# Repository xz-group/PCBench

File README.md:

# PCBench

PCBench is a free open-source benckmark for board-level hardware attacks and Trojans.

## What's News

Version 1.0

This is the initial release of the benchmars for board-level hardware security.

## Motivation
Most modern electronic systems are hosted by printed circuit boards(PCBs), making them a ubiquitous system component that can take many different shapes and forms. In order to achieve a high level of economy of scale, the global supply chain of electronic systems has evolved into disparate segments for the design, fabrication, assembly, and testing of PCB boards and their various associated components. <br />
As a consequence, the modern PCB supply chain exposes many vulnerabilities along its different stages, allowing adversaries to introduce malicious alterations to facilitate board-level attacks. As an emerging hardware threat, the attack and defense techniques at the board level have not yet been systemically explored and thus require a thorough and comprehensive investigation. <br />
In the absence of a standard board-level attack benchmark, current re-search on perspective countermeasures is likely to be evaluated on proprietary variants of ad-hoc attacks, preventing credible and verifiable comparison among different techniques. Upon this request, we have created the PCBench, which is a set of board-level attack benchmarks for open-source release.

## Benchmarking Methodology

We generated the benchmarks based on the methodology proposed in our **ASP-DAC 2021 paper: *[PCBench: Benchmarking of Board-Level Hardware Attacks and Trojans](http://jin.ece.ufl.edu/papers/ASPDAC2021_PCB.PDF)***.
In this paper, we systematically defined and categorized a broad range of board-level attacks. 
For the first time, the attack vectors and construction rules for board-level attacks were developed.
A practical and reliable board-level attack benchmark generation scheme was also developed, which can be used to produce references for evaluating countermeasures.

## Released Benchmarks
To facilitate the development of board-level attack benchmarks, representative circuit boards are chosen as the victim designs. 
Open-source hardware projects are mainly selected due to their modern design styles, the availability of PCB designs as well as detailed documents, firmware, and/or application software. 
As a result, researchers can easily reconstruct the board-level security evaluation benchmarks. 

**The following table lists the released benchmarks:**

 Design Name | Description | Dimension (mm^2) | No. of Components | No. of Layers
 ----------- | ----------- | :---------: | :-----------------: | :-------------:
 [arduino-due](arduino-due) | Microcontroller devlopment board based on ATsam3x8e with ARM Cortex-M3 core | 102x53 | 141 | 2
 [a13-olinuxino](a13-olinuxino-g2) | Single-board Linux computer based on Allwinner-A13 with Cortex-A8 core | 120x120|370|4

*This is not the full list of benchmarks as we continue developing the new benchmarks.* 

The fabricated Arduino-due board with and without Trojans are shown below.

## Contributiors
The PCBench is mainly developed by *Huifeng Zhu* and *[Dr.Silvia Zhang](https://xzgroup.wustl.edu/people/xuan-silvia-zhang/)* from *Washington University in St.Louis*; *[Dr.Yier Jin](http://jin.ece.ufl.edu/)* from the *University of Florida*; and *[Dr.Xiaolong Guo](https://www.ece.k-state.edu/people/faculty/guo/)* from *Kansas State University*.

We also appreciate the efforts of below contributors: 

## How to Refer to PCBench?
If you are using the benchmarks provided in PCBench to develop either threat mitigation methods or new threat exploitations, please cite our official paper of PCBench. 
You can find the paper in the website of IEEE: [link]() or at [link](http://jin.ece.ufl.edu/papers/ASPDAC2021_PCB.PDF).

A typical BibTeX citation would be, for example:
```
@software{PCBench,
  author = {Huifeng Zhu and Xiaolong Guo and Yier Jin and Xuan Zhang}, % actual author and maintainer
  title = {PCBench: Benchmarking of Board-Level Hardware Attacks and Trojans},
  booktitle = {26th Asia and South Pacific Design Automation Conference (ASP-DAC)},
  year = {2021},
  url = {https://github.com/xz-group/PCBench},
  version = {1.0},
  date = {2020-10-15}, % set to the release date
}
```
## Get Feedback
Feel free to contact us if you have questions about PCBench: **Huifeng Zhu (zhuhuifeng@wustl.edu)**.

## License

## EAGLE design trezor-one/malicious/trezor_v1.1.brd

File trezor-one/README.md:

# Trezor One Benchmark

https://trezor.io/

## High-level Description of Hardware Attack
The goal of the Trezor One Benchmark is to siphon the recovery seed from a Trezor One device. This information could then be used to retrieve the original cryptocurrency passwords stored by the user. The recovery process is used in the event that the user forgets their PIN number or enters too many incorrect attempts. The user manual outlines this [recovery process](https://wiki.trezor.io/User_manual:Recovery).

During the initial startup sequence of the Trezor One, the user is instructed to write down a unique, device-generated sequence of 24 english words. Each word is displayed one at a time on the Trezor's built-in monochrome display.

This attack describes the necessary steps for capturing packets of display data and decoding them to reveal the full recovery seed.

## Data Capture
The Trezor One Victim board is equipped with a malicious ATtiny microcontroller that is attached, in a slave configuration, to the Trezor's STM32 microcontroller SPI lines. These SPI lines are also connected the the Trezor's display and are used to send bitmap image data. This configuration allows the malicious ATtiny to go undetected while still having access to all data being sent from the Trezor's microcontroller to its display.

Due to how the display operates, the Trezor's microcontroller sends a complete bitmap image to the display each time it needs to be altered, regardless of how many pixels need to change. This is beneficial because it makes it easy to decode recorded SPI packets and rebuild them into complete images. These decoded images represent exactly, pixel for pixel, what was displayed on the Trezor device at the time of packet transmission.

## Implementing the Attack

### Technical Details

#### Display Connecter Pins Table:

| PIN | <------------> | NET |
| ----------- | ----------- | ----------- |
| 12 | <------------> | GND |
| 13 | <------------> | SPI ENABLE |
| 15 | <------------> | DISPLAY DATA/COMMAND |
| 18 | <------------> | SPI CLOCK |
| 19 | <------------> | SPI DATA |

#### Trezor SSD1306 Operation
The display used is a 128x64 OLED SPI display. Internally, the display contains a single-chip driver called the SSD1306 which is widely utilized and documented. The full details of the [SSD1306 documentation](https://cdn-shop.adafruit.com/datasheets/SSD1306.pdf) are crucial to gaining a low-level understanding of this attack. 

A full screen's worth of data is sent to the display each time it is updated. At a simple level, there are 8,192 total pixels and each pixel is driven by a 1 for ON or 0 for OFF. This series of 1024 1's and 0's are sent one byte at a time via SPI to the display. However, they are not ordered left to right and top to bottom as one might expect. The full details of the pixel mapping algorithm is outlined on page 25 of the [SSD1306 documentation](https://cdn-shop.adafruit.com/datasheets/SSD1306.pdf) with regards to the display's GDDRAM. This process needs to be reversed for decoding and is exactly what is embedded in the [src/image_builder.py](image_builder.py) script.

Along with the 8,192 data bits that are sent to the display, there are also command sequences that are sent at the beginning of each transmission that do not represent pixel values. Outlined below is information representing the series of bits sent via SPI to the display by the Trezor. If necessary, specific command bytes can be tracked down in the [Trezor Firmware](https://github.com/trezor/trezor-mcu).

* **Setup Command Bytes (25 total)**
    * Description: The setup command bytes are sent directly after the RESET line of the display is triggered on startup. They aid in resetting the display, setting the contrast, setting the page addressing mode, etc. The exact bytes and corresponding meaning can be found in the [oled.c](https://github.com/trezor/trezor-mcu/blob/8af1f3643651e1cbee6b6196401f9c63e7cfc0f9/oled.c) file in the [Trezor Firmware](https://github.com/trezor/trezor-mcu).
    * Data: {0xAE, 0xD5, 0x80, 0xA8, 0x3F, 0xD3, 0x00, 0x40, 0x8D, 0x14, 0x20, 0x00, 0xA1, 0xC8, 0xDA, 0x12, 0x81, 0xCF, 0xD9, 0xF1, 0xDB, 0x40, 0xA4, 0xA6, 0xAF}
* **Prepended Command Bytes (3 total)**
    * Description: The prepended command bytes are sent directly before new image data is sent. For the Trezor, these bytes are always the same and can be helpful as a delimiter for debugging purposes.
    * Data: {0x00, 0x10, 0x40}
* **Pixel Value Bytes (1024 total)**
* Description: The pixel value bytes represent 1's and 0's for each of the 8,192 pixels. This means that there are 1024 SPI byte packets sent for this part of the transmission. This is the most important part of the transmission for the attack and is the only piece that needs to be recorded to EEPROM since the other pieces are constant and predictable.
* Data: {0x__, 0x__, 0x__, .......}

It is important to note that there is a signal connected to the display (DISPLAY DATA/COMMAND or D/C) that tells the display whether the incoming data is a series of command bytes or data bytes. For the Setup and Prepended Command Bytes, the D/C pin is pulled low so that the data is transferred to the SSD1306 command register. For the Pixel Value Bytes, the D/C is pulled high to be treated as data.

The order in which these command bytes and data bytes are sent is consistent:
1. The Setup Command Bytes are sent only once when the device is powered on.
1. The Preprended Command Bytes are sent before the initial screen data is sent.
1. The Pixel Value Bytes are sent as 0's (1024 bytes of 0x00) to clear the GDDRAM of the SSD1306.
1. The Preprended Command Bytes are sent before the startup screen data is sent.
1. The Pixel Value Bytes are sent to display the startup screen.
1. The previous two steps are repeated for every subsequent image displayed. This means that subsequent transmissions are a total of 1027 bytes (3 Prepend Command Bytes + 1024 Pixel Value Bytes)

Manual tests with an Arduino board and an external 128x64 OLED SPI display can be used to test what unique outputs may look like. Modify [SPI_Manual_Test.ino](/src/SPI_Manual_Test/SPI_Manual_Test.ino) for testing.

### Ideal Attack Sequence
1. Program the malicious ATtiny chip with firmware that enables it to record and store SPI packets to EEPROM.
1. After Trezor device is setup and functional, the malicious ATtiny chip will contain the SPI packets relating to the recovery seed image data. This means that the ATtiny device can now be connected to in some fashion that allows for its EEPROM to be extracted.
1. Enter the extracted EEPROM bytes into a .csv file.
1. Run the image builder Python script that converts the data in the .csv file to a .png image.
1. Repeat the previous step until all images representing each word in the recovery seed are created.
1. Use the recovery seed to gain access to the information on the Trezor device by following the [recovery process](https://wiki.trezor.io/User_manual:Recovery).

### Proof of Concept Attack Sequence
To prove that this ideal attack sequence is possible, various methods and tools were used to extract test data from a from both a real Trezor One and a Trezor victim board.

First, a Trezor victim board was populated. Firmware was built and uploaded by following the [Trezor One Dev Kit](https://mcudev.github.io/trezor-dev-kit/) documentation. Once the device is set up, you must navigate to trezor.io/start and follow the instructions. Unfortunately, this process involves updating the firmware which seems to halt any progress past this point. After the forced update, the Trezor displays an "Unknown bootloader detected" warning and does not work. However, for the purposes of the proof of concept, this limitation was ignored because the SPI data packets used to display the startup screen and "Unknown bootloader detected" warning are of the same format as the packets used to display all content (including the recovery seed words).

Next, a logic analyzer was connected to the necessary pins on the display connector (see Technical Details) using an improvised connector. The HEX values sent over the SPI data line were then exported to the [startup_spi_data.csv](src/startup_spi_data.csv) file. The beginning and ending of the 1024 bytes representing each displayed image were then set manually in the [image_builder.py](src/image_builder.py) file. At this point in testing, the Trezor victim board displayed two images on startup. The first was a lock icon and the second was the "Unknown bootloader detected" warning. Setting and running the python script for both sets of 1024 bytes in the .csv file resulted in the [Lock Screen Image](src/lock_screen.png) and [Info Screen Image](src/info_screen.png) being generated.

To prove that these results were relevant to a real Trezor, the improvised connector was placed on a geniune Trezor One. Using a logic analyzer in the same fashion resulted in the [real_trezor_startup.csv](src/real_trezor_startup.csv) file. After setting the start and end rows of the SPI data relating to the startup screen, the python script produced the [real_trezor_startup.png](src/real_trezor_startup.png) image.

### Further Implementation

Currently, there is one gap between the proof of concept and the ideal attack sequence. In the proof of concept, the SPI data was captured with a logic analyzer and then exported to .csv file. In the ideal attack sequence, the ATtiny captures the data and the user then connects to the ATtiny to extract the recorded data from EEPROM.

Firmware for the ATtiny needs to be written that implements it as an SPI slave. Since the general purpose SPI library does not support the ATtiny85 being used, a more primitive script must be used. Refer to this [stackexchange post](https://electronics.stackexchange.com/questions/60114/spi-h-for-attiny) for ideas.

Once this is implemented, the next immediate problem is EEPROM space. It must be noted that the data has to be held in EEPROM because it needs to be stored in non-volatile memory. The Trezor will be powered off before the data extraction from the ATtiny occurs. It seems that the ATtiny85 has 512 bytes of EEPROM. Unfortunately, this is nowhere near sufficient for this application. Ideally, 24,576 bytes (24 recovery screens * 1024 bytes per display image) would be available to record the SPI data to. This also assumes that the ATtiny is equipped with code that knows exactly which SPI packets will represent the 24 recovery screens that need to be recorded. On the surface, this may seem simple to account for. In the startup sequence, the recovery screens should always be the Nth screen to be displayed. The ATtiny would then be able to count packets until it gets to the Nth screen. However, this may not work because of variants such as the unnecessary button presses from the user that result in extra screens being displayed. Therefore, a better method will probably have to be utilized. One method would be to figure out if the recovery screens have a special, unique design. For example, as shown in this [photo](trezor-one-confirm-seed.jpeg), the ATtiny could be programmed with a bitmap that has the correct bytes representing "Write down the seed" and "Nth word is:." These could then be compared with the most recently recorded packet to decide whether or not the packet represent a recovery screen. Furthermore, this method can also help reduce necessary EEPROM space. It can be noted than in the [photo](trezor-one-confirm-seed.jpeg), takes up at most 1/3 of the vertical space and slightly more than 1/2 of the horizontal space. While this can't solve the 512 byte limitation, it can greatly reduce the EEPROM size needed to well under 24,576 bytes. Since the final EEPROM size needed will be greater than the currently available 512 bytes in the ATtiny85, there are two options. The first is to choose another microcontroller with a larger EEPROM. The second option would be to add an external EEPROM chip which is cheap and offers a tremendous amount of storage. However, one caveat of the latter method is that the external EEPROM would need to be connected over SPI. This may potentially pose a problem because the microcontroller would have to act as both and SPI slave for the STM32 and a master for the external EEPROM.

### ATtiny85-20M1 Breakout Board

In order to upload code to this ATtiny85 package for testing, a custom breakout board is needed. This is because the footprint is unique and compatible breakout boards are difficult to find online. This breakout board was designed in KiCad and an image of the board along with the pinout information is listed below. All design files can be found [here](attiny85_breakout_board).

| Header Pin | ATtiny85 Pin | Connection |
| ----------- | ----------- | ----------- |
| 1 | 1 | RESET/PB5 |
| 2 | 2 | XTAL1/PB3 |
| 5 | 5 | XTAL2/PB4 |
| 8 | 8 | GND |
| 11 | 11 | AREF/PB0 |
| 12 | 12 | PB1 |
| 14 | 14 | PB2 |
| 15 | 15 | VCC |

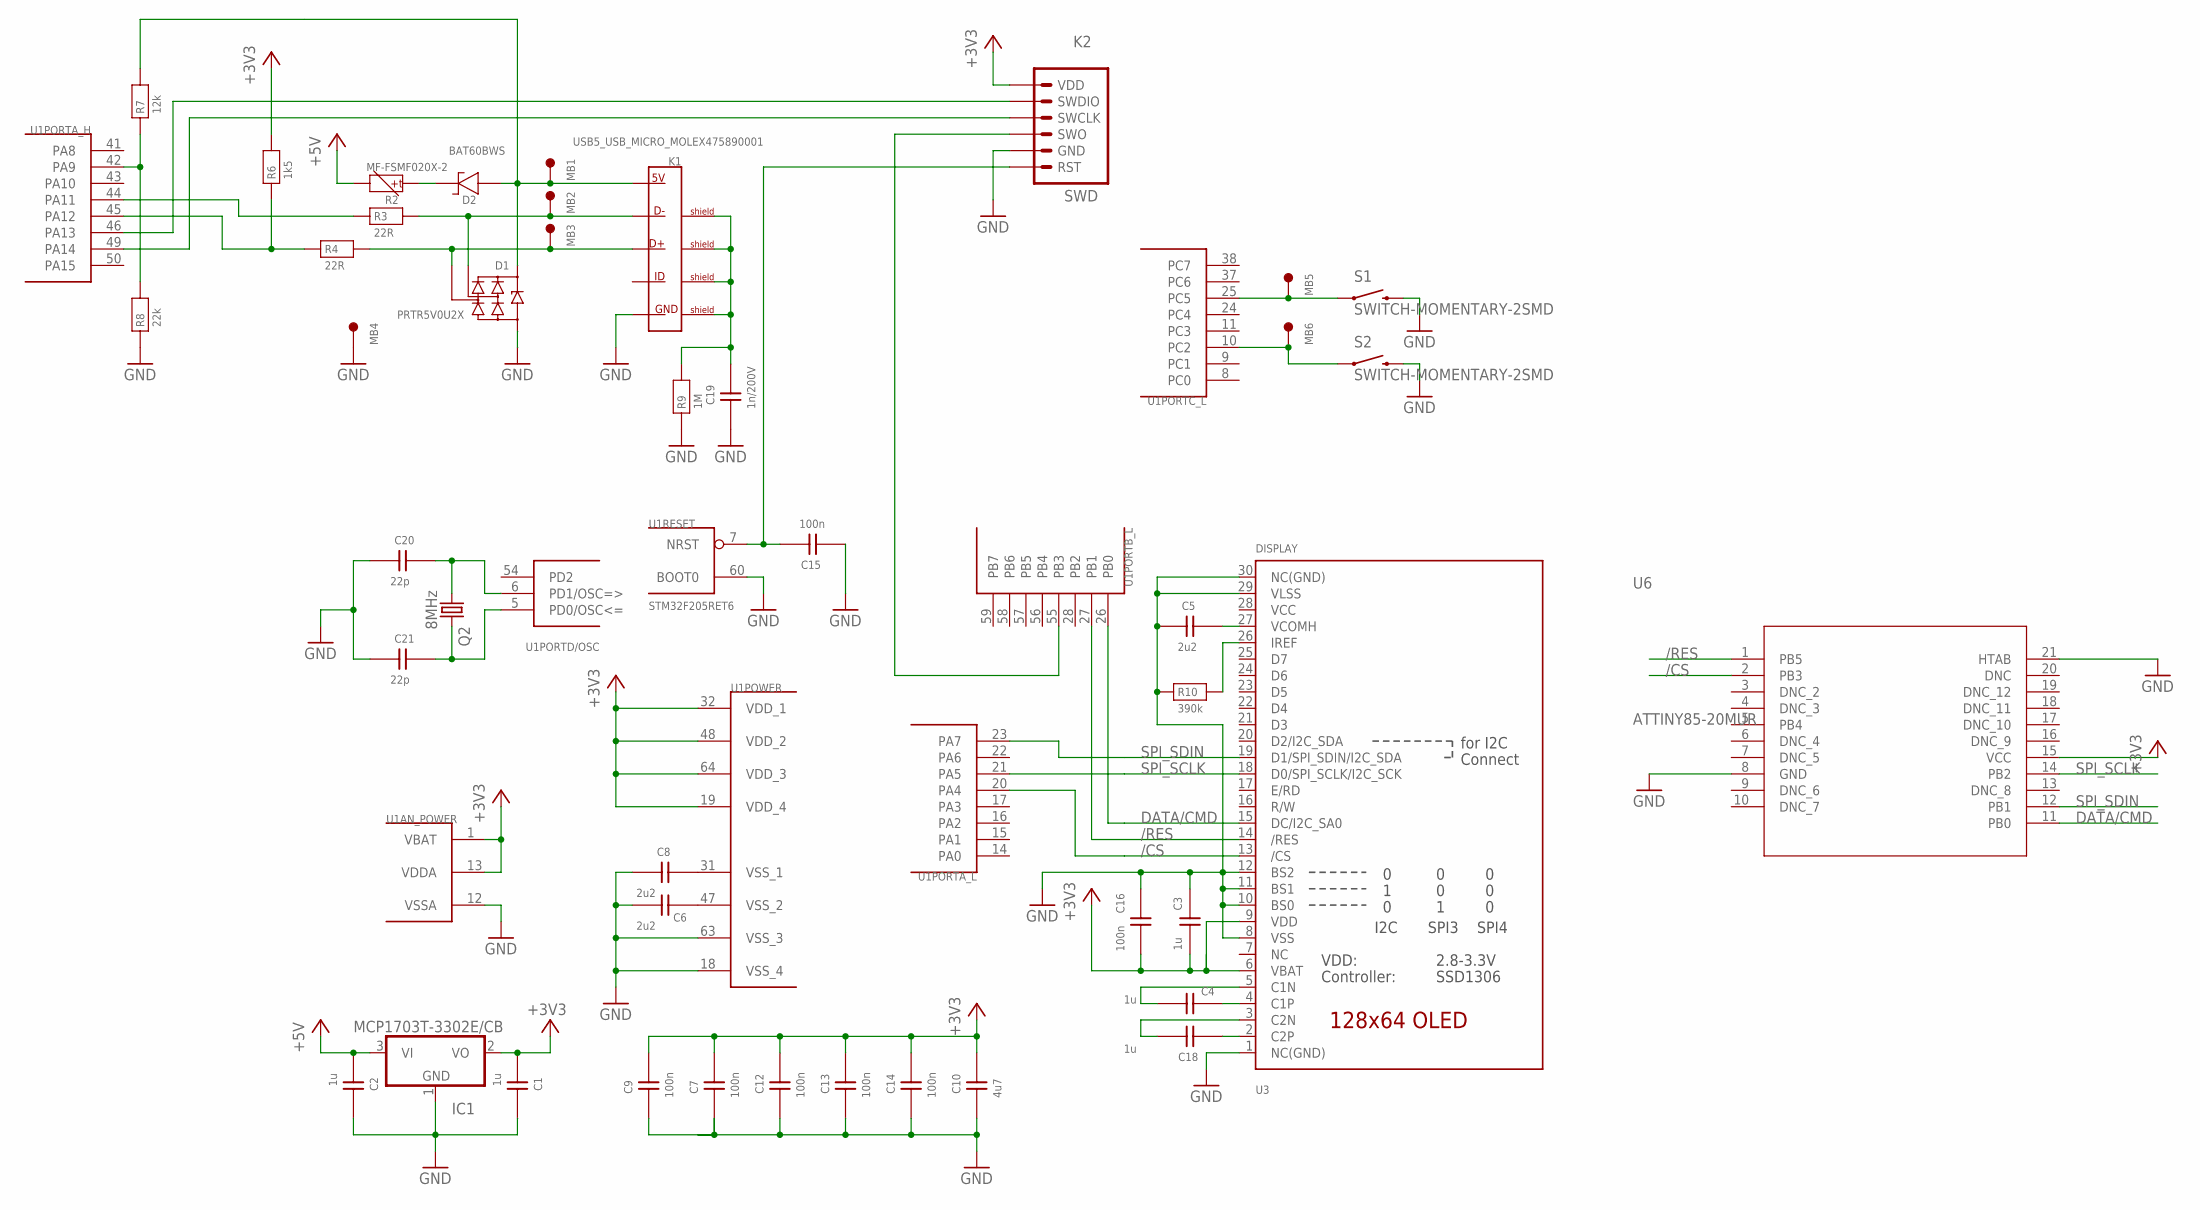
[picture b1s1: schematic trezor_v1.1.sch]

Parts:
C1, C2, C3, C4, C18: 1u; 0402
C5: 2u2; 0603
C6, C8: 2u2; 0402
C7, C9, C12, C13, C14, C15, C16: 100n; 0402
C10: 4u7; 0603
C19: 1n/200V; 0603
C20, C21: 22p; 0402
D1: PRTR5V0U2X; SOT143B
D2: BAT60BWS; SOD323
IC1: MCP1703T-3302E/CB; SOT23
K1: USB5_USB_MICRO_MOLEX475890001; USB_MICRO-MOLEX475890001
K2: SWD
MB1, MB2, MB3, MB4, MB5, MB6: MB_1.50; MB1.5
Q2: 8MHz; CTS406
R2: MF-FSMF020X-2; 0603
R3, R4: 22R; 0402
R6: 1k5; 0402
R7: 12k; 0402
R8: 22k; 0402
R9: 1M; 0603
R10: 390k; 0402
S1, S2: SWITCH-MOMENTARY-2SMD; TACTILE_SWITCH_SMD
U1: STM32F205RET6; TQFP64
U3: DISPLAY; UG-2864HSWEG01_0.96IN_WRAPAROUND
U6: ATTINY85-20MUR; 20M1_ATM

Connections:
+3V3: C1.P$1 (1), C3.P$1 (1), C7.P$2 (2), C9.P$2 (2), C10.2, C12.P$2 (2), C13.P$2 (2), C14.P$2 (2), C16.P$1 (1), IC1.2 (VO), K2.6 (VDD), R6.P$2 (2), U1.1 (VBAT), U1.13 (VDDA), U1.19 (VDD_4), U1.32 (VDD_1), U1.48 (VDD_2), U1.64 (VDD_3), U3.6 (VBAT), U3.9 (VDD), U6.15 (VCC)
+5V: C2.P$1 (1), IC1.3 (VI), R2.2
/CS: U1.20 (PA4), U3.13 (/CS), U6.2 (PB3)
/RES: U1.27 (PB1), U3.14 (/RES), U6.1 (PB5)
DATA/CMD: U1.26 (PB0), U3.15 (DC/I2C_SA0), U6.11 (PB0)
GND: C1.P$2 (2), C2.P$2 (2), C3.P$2 (2), C5.1, C6.P$1 (1), C7.P$1 (1), C8.P$1 (1), C9.P$1 (1), C10.1, C12.P$1 (1), C13.P$1 (1), C14.P$1 (1), C15.P$1 (1), C16.P$2 (2), C19.1, C20.P$1 (1), C21.P$1 (1), D1.1 (GND), IC1.1 (GND), K1.5 (5_GND), K2.2 (GND), MB4.1, R8.P$1 (1), R9.1, R10.P$1 (1), S1.3 (2), S1.4 (2), S2.3 (2), S2.4 (2), U1.12 (VSSA), U1.18 (VSS_4), U1.60 (BOOT0), U1.63 (VSS_3), U3.1 (NC(GND)), U3.8 (VSS), U3.10 (BS0), U3.11 (BS1), U3.12 (BS2), U3.29 (VLSS), U3.30 (NC(GND)), U6.8 (GND), U6.21 (HTAB)
unnamed: C15.P$2 (2), K2.1 (RST), U1.7 (NRST)
unnamed: C8.P$2 (2), U1.31 (VSS_1)
unnamed: C5.2, U3.27 (VCOMH)
unnamed: C6.P$2 (2), U1.47 (VSS_2)
unnamed: R10.P$2 (2), U3.26 (IREF)
unnamed: C18.P$1 (1), U3.2 (C2P)
unnamed: C4.P$1 (1), U3.4 (C1P)
unnamed: C18.P$2 (2), U3.3 (C2N)
unnamed: C4.P$2 (2), U3.5 (C1N)
unnamed: K2.3 (SWO), U1.55 (PB3)
unnamed: K2.5 (SWDIO), U1.46 (PA13)
unnamed: K2.4 (SWCLK), U1.49 (PA14)
unnamed: R3.P$1 (1), U1.44 (PA11)
unnamed: MB5.1, S1.1, S1.2 (1), U1.25 (PC5)
unnamed: MB6.1, S2.1, S2.2 (1), U1.10 (PC2)
unnamed: D1.4 (VCC), D2.A (1), K1.1 (1_5V), MB1.1, R7.P$2 (2)
unnamed: D2.K (2), R2.1
unnamed: D1.2 (I/O1), K1.2 (2_D-), MB2.1, R3.P$2 (2)
unnamed: D1.3 (I/O2), K1.3 (3_D+), MB3.1, R4.P$2 (2)
unnamed: C19.2, K1.S1_BOT (SHIELD_1), K1.S1_TOP (SHIELD_1), K1.S2_BOT (SHIELD_2), K1.S2_TOP (SHIELD_2), K1.S3_BOT (SHIELD_3), K1.S3_TOP (SHIELD_3), K1.S4_BOT (SHIELD_4), K1.S4_TOP (SHIELD_4), K1.SA (SHIELD_1), K1.SB (SHIELD_2), R9.2
unnamed: R7.P$1 (1), R8.P$2 (2), U1.42 (PA9)
SPI_SCLK: U1.21 (PA5), U3.18 (D0/SPI_SCLK/I2C_SCK), U6.14 (PB2)
SPI_SDIN: U1.23 (PA7), U3.19 (D1/SPI_SDIN/I2C_SDA), U6.12 (PB1)
USB_D_P: R4.P$1 (1), R6.P$1 (1), U1.45 (PA12)
VCC: U3.28 (VCC)
XTAL1: C20.P$2 (2), Q2.1, U1.6 (PD1/OSC=>)
XTAL2: C21.P$2 (2), Q2.3 (2), U1.5 (PD0/OSC<=)

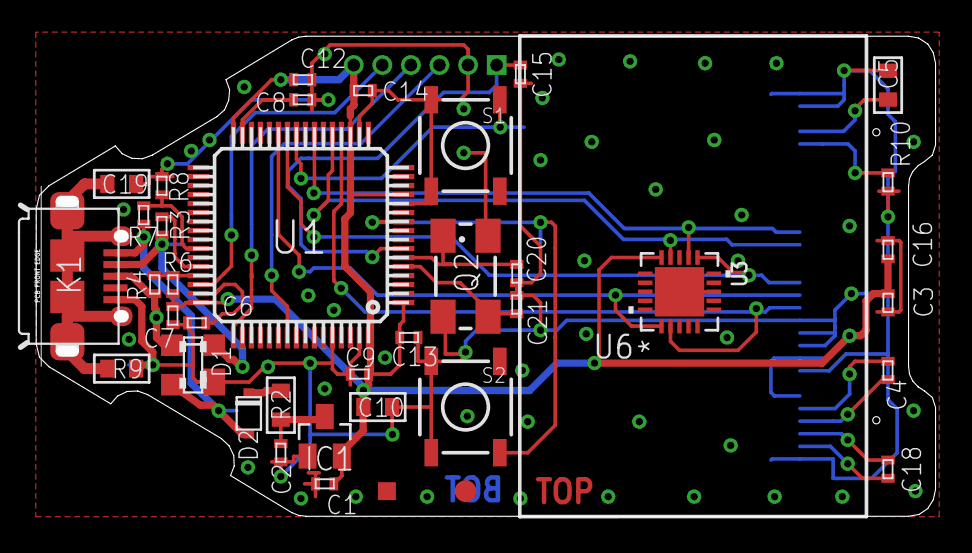
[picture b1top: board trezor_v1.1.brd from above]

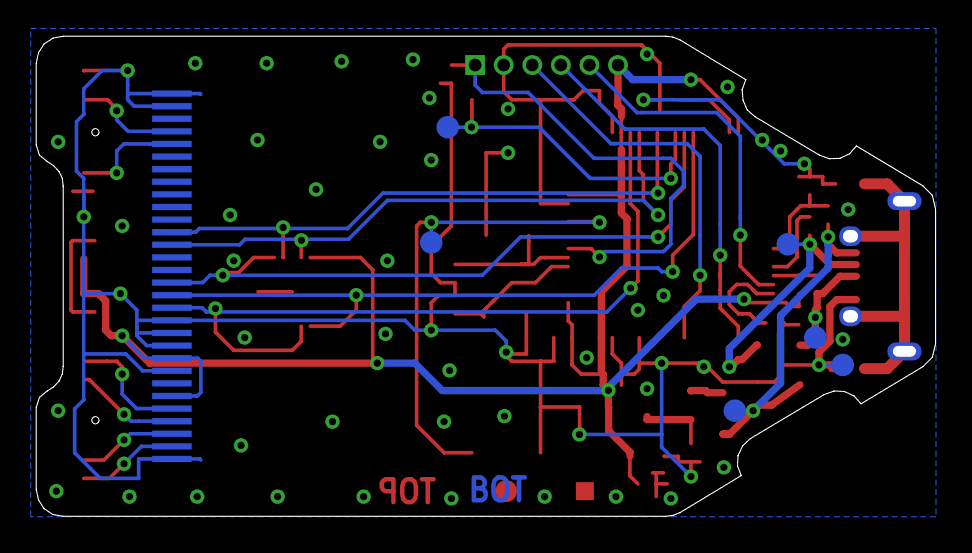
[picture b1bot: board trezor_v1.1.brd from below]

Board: 2 copper layers, 50.0 x 26.7 mm, 46 parts (6 on the bottom side), 32 nets.

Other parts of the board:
U$3: BADMARK
U$4: CENTR

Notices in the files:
parts and their libraries:
Arduino-utility: Copyright (c) 2016-2017 Arduino LLC.  All right reserved.
COPYRIGHT: Copyright (C) 2018 Accelerated Designs. All rights reserved
microbuilder: This work is placed in the public domain, and may be freely used for commercial and non-commercial work with the following conditions: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
